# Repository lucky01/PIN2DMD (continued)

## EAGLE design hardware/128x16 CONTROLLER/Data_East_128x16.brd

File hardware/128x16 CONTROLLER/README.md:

# PIN2DMD - 128x16 DOT MATRIX CONTROLLER BOARD

This are the PCB files for the Dot Matrix Contoller Board like used in early Data East machines 
e.g Checkpoint, Hook, Star Trek and Teenage Mutant Ninja Turtles. It is needed to connect these
machines to the PIN2DMD Nucleo shield. PCB design by Rappelbox, UncleSash and Lucky1

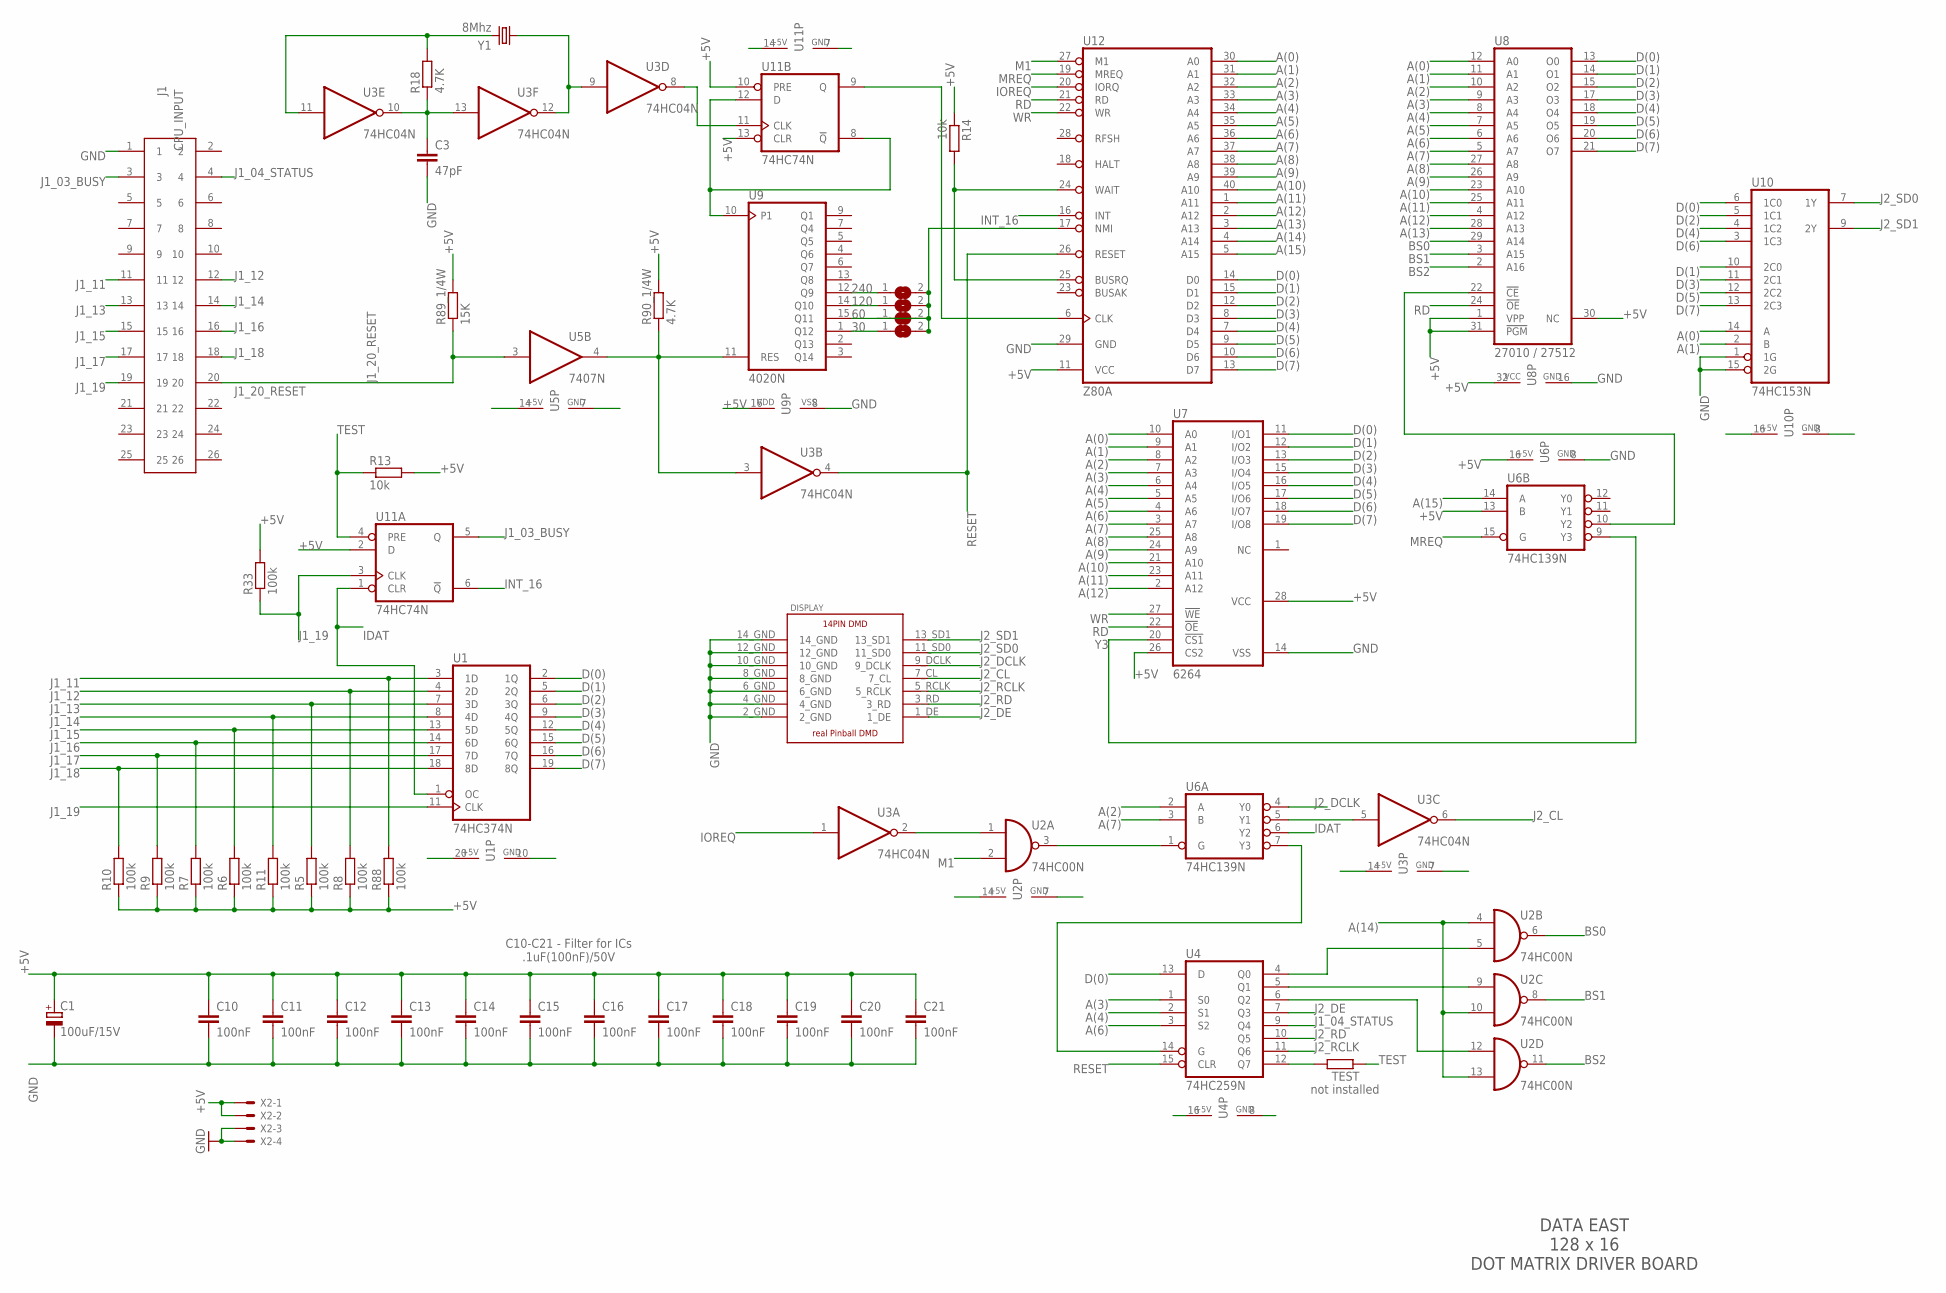
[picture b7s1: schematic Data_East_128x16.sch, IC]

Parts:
C1: 100uF/15V; E2,5-7
C3: 47pF; C050-025X075
C10, C11, C12, C13, C14, C15, C16, C17, C18, C19, C20, C21: 100nF; C050-025X075
CPU_INPUT: J1; 61202622323
DISPLAY: PINBALL_DMD_HEADER_MALE; 14_PIN_DMD_MALE
R5, R6, R7, R8, R9, R10, R11, R33, R88: 100k; 0207/7
R13, R14: 10k; 0207/7
R18, R90_1/4W: 4.7K; 0207/7
R89_1/4W: 15K; 0207/7
SJ2, SJ4, SJ5, SJ6: SJ
TEST: R-EU_0207/7; 0207/7
U1: 74HC374N; DIL20
U2: 74HC00N; DIL14
U3: 74HC04N; DIL14
U4: 74HC259N; DIL16
U5: 7407N; DIL14
U6: 74HC139N; DIL16
U7: 6264; DIL28-6
U8: 27010 / 27512; DIL32
U9: 4020N; DIL16
U10: 74HC153N; DIL16
U11: 74HC74N; DIL14
U12: Z80A; DIL40
X2: KK-156-4
Y1: 8Mhz; HC49U70

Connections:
30: SJ6.1, U9.1 (Q12)
60: SJ2.2, SJ4.2, SJ5.1, SJ5.2, SJ6.2, U9.15 (Q11), U12.17 (NMI)
120: SJ4.1, U9.14 (Q10)
240: SJ2.1, U9.12 (Q9)
+5V: C1.+, C10.1, C11.1, C12.1, C13.1, C14.1, C15.1, C16.1, C17.1, C18.1, C19.1, C20.1, C21.1, R5.1, R6.1, R7.1, R8.1, R9.1, R10.1, R11.1, R13.2, R14.1, R33.2, R88.1, R89_1/4W.2, R90_1/4W.2, U1.20 (VCC), U2.14 (VCC), U3.14 (VCC), U4.16 (VCC), U5.14 (VCC), U6.13 (B), U6.16 (VCC), U7.26 (CS2), U7.28 (VCC), U8.1 (VPP), U8.30 (NC), U8.31 (!PGM), U8.32 (VCC), U9.16 (VDD), U10.16 (VCC), U11.2 (D), U11.10 (PRE), U11.13 (CLR), U11.14 (VCC), U12.11 (VCC), X2.1, X2.2
A(0): U7.10 (A0), U8.12 (A0), U10.14 (A), U12.30 (A0)
A(1): U7.9 (A1), U8.11 (A1), U10.2 (B), U12.31 (A1)
A(2): U6.2 (A), U7.8 (A2), U8.10 (A2), U12.32 (A2)
A(3): U4.1 (S0), U7.7 (A3), U8.9 (A3), U12.33 (A3)
A(4): U4.2 (S1), U7.6 (A4), U8.8 (A4), U12.34 (A4)
A(5): U7.5 (A5), U8.7 (A5), U12.35 (A5)
A(6): U4.3 (S2), U7.4 (A6), U8.6 (A6), U12.36 (A6)
A(7): U6.3 (B), U7.3 (A7), U8.5 (A7), U12.37 (A7)
A(8): U7.25 (A8), U8.27 (A8), U12.38 (A8)
A(9): U7.24 (A9), U8.26 (A9), U12.39 (A9)
A(10): U7.21 (A10), U8.23 (A10), U12.40 (A10)
A(11): U7.23 (A11), U8.25 (A11), U12.1 (A11)
A(12): U7.2 (A12), U8.4 (A12), U12.2 (A12)
A(13): U8.28 (A13), U12.3 (A13)
A(14): U2.4 (I0), U2.10 (I1), U2.13 (I1), U12.4 (A14)
A(15): U6.14 (A), U12.5 (A15)
BS0: U2.6 (O), U8.29 (A14)
BS1: U2.8 (O), U8.3 (A15)
BS2: U2.11 (O), U8.2 (A16)
D(0): U1.2 (1Q), U4.13 (D), U7.11 (I/O1), U8.13 (O0), U10.6 (1C0), U12.14 (D0)
D(1): U1.5 (2Q), U7.12 (I/O2), U8.14 (O1), U10.10 (2C0), U12.15 (D1)
D(2): U1.6 (3Q), U7.13 (I/O3), U8.15 (O2), U10.5 (1C1), U12.12 (D2)
D(3): U1.9 (4Q), U7.15 (I/O4), U8.17 (O3), U10.11 (2C1), U12.8 (D3)
D(4): U1.12 (5Q), U7.16 (I/O5), U8.18 (O4), U10.4 (1C2), U12.7 (D4)
D(5): U1.15 (6Q), U7.17 (I/O6), U8.19 (O5), U10.12 (2C2), U12.9 (D5)
D(6): U1.16 (7Q), U7.18 (I/O7), U8.20 (O6), U10.3 (1C3), U12.10 (D6)
D(7): U1.19 (8Q), U7.19 (I/O8), U8.21 (O7), U10.13 (2C3), U12.13 (D7)
GND: C1.-, C3.2, C10.2, C11.2, C12.2, C13.2, C14.2, C15.2, C16.2, C17.2, C18.2, C19.2, C20.2, C21.2, CPU_INPUT.1, DISPLAY.2_GND, DISPLAY.4_GND, DISPLAY.6_GND, DISPLAY.8_GND, DISPLAY.10_GND, DISPLAY.12_GND, DISPLAY.14_GND, U1.10 (GND), U2.7 (GND), U3.7 (GND), U4.8 (GND), U5.7 (GND), U6.8 (GND), U7.14 (VSS), U8.16 (GND), U9.8 (VSS), U10.1 (1G), U10.8 (GND), U10.15 (2G), U11.7 (GND), U12.29 (GND), X2.3, X2.4
IDAT: U1.1 (OC), U6.6 (Y2), U11.1 (CLR)
INT_16: U11.6 (!Q), U12.16 (INT)
IOREQ: U3.1 (I), U12.20 (IORQ)
J1_03_BUSY: CPU_INPUT.3, U11.5 (Q)
J1_04_STATUS: CPU_INPUT.4, U4.9 (Q4)
J1_11: CPU_INPUT.11, R88.2, U1.3 (1D)
J1_12: CPU_INPUT.12, R8.2, U1.4 (2D)
J1_13: CPU_INPUT.13, R5.2, U1.7 (3D)
J1_14: CPU_INPUT.14, R11.2, U1.8 (4D)
J1_15: CPU_INPUT.15, R6.2, U1.13 (5D)
J1_16: CPU_INPUT.16, R7.2, U1.14 (6D)
J1_17: CPU_INPUT.17, R9.2, U1.17 (7D)
J1_18: CPU_INPUT.18, R10.2, U1.18 (8D)
J1_19: CPU_INPUT.19, R33.1, U1.11 (CLK), U11.3 (CLK)
J1_20_RESET: CPU_INPUT.20, R89_1/4W.1, U5.3 (I)
J2_CL: DISPLAY.7_CL, U3.6 (O)
J2_DCLK: DISPLAY.9_DCLK, U6.4 (Y0)
J2_DE: DISPLAY.1_DE, U4.7 (Q3)
J2_RCLK: DISPLAY.5_RCLK, U4.11 (Q6)
J2_RD: DISPLAY.3_RD, U4.10 (Q5)
J2_SD0: DISPLAY.11_SD0, U10.7 (1Y)
J2_SD1: DISPLAY.13_SD1, U10.9 (2Y)
M1: U2.2 (I1), U12.27 (M1)
MREQ: U6.15 (G), U12.19 (MREQ)
unnamed: C3.1, R18.1, U3.10 (O), U3.13 (I)
unnamed: R18.2, U3.11 (I), Y1.2
unnamed: U3.9 (I), U3.12 (O), Y1.1
unnamed: TEST.2, U4.12 (Q7)
unnamed: U3.8 (O), U11.11 (CLK)
unnamed: U9.10 (P1), U11.8 (!Q), U11.12 (D)
unnamed: R90_1/4W.1, U3.3 (I), U5.4 (O), U9.11 (RES)
unnamed: U11.9 (Q), U12.6 (CLK)
unnamed: R14.2, U12.24 (WAIT), U12.25 (BUSRQ)
unnamed: U3.5 (I), U6.5 (Y1)
unnamed: U2.5 (I1), U4.4 (Q0)
unnamed: U2.1 (I0), U3.2 (O)
unnamed: U2.3 (O), U6.1 (G)
unnamed: U2.9 (I0), U4.5 (Q1)
unnamed: U4.14 (G), U6.7 (Y3)
unnamed: U2.12 (I0), U4.6 (Q2)
unnamed: U6.10 (Y2), U8.22 (!CE)
RD: U7.22 (!OE), U8.24 (!OE), U12.21 (RD)
RESET: U3.4 (O), U4.15 (CLR), U12.26 (RESET)
TEST: R13.1, TEST.1, U11.4 (PRE)
WR: U7.27 (!WE), U12.22 (WR)
Y3: U6.9 (Y3), U7.20 (!CS1)

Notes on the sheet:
C10-C21 - Filter for ICs .1uF(100nF)/50V
DATA EAST 128 x 16 DOT MATRIX DRIVER BOARD
not installed

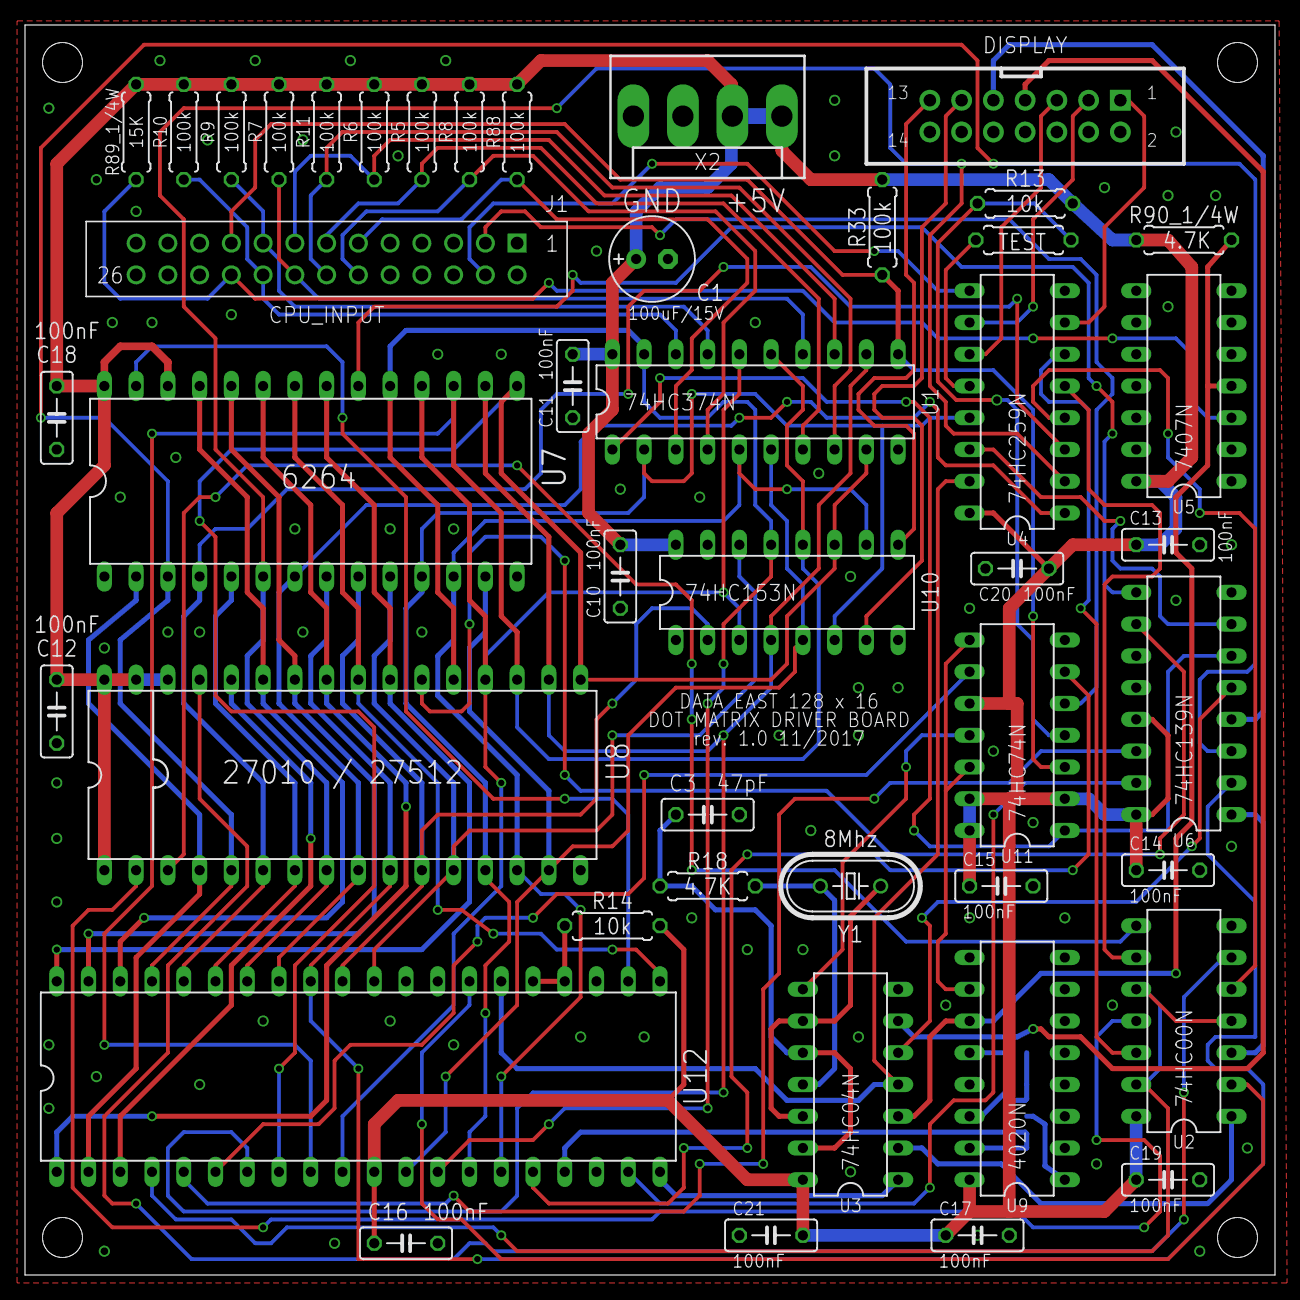
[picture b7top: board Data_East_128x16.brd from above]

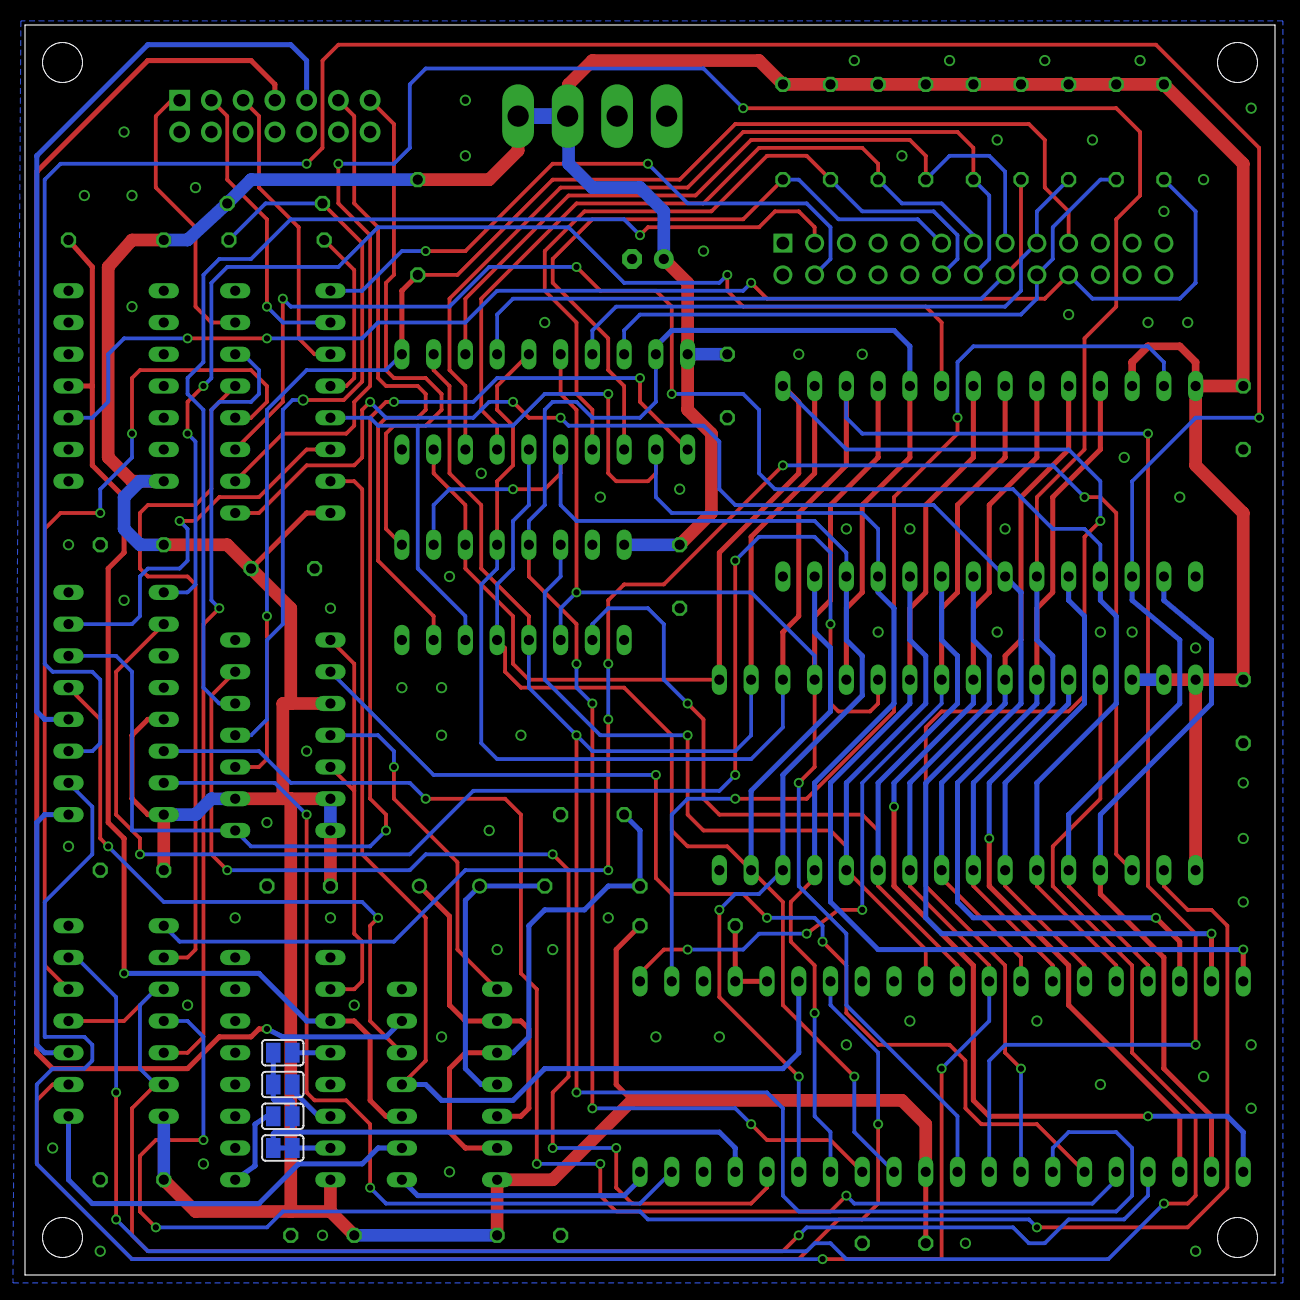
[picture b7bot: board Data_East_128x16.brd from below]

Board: 2 copper layers, 100.0 x 100.0 mm, 49 parts (4 on the bottom side), 79 nets.

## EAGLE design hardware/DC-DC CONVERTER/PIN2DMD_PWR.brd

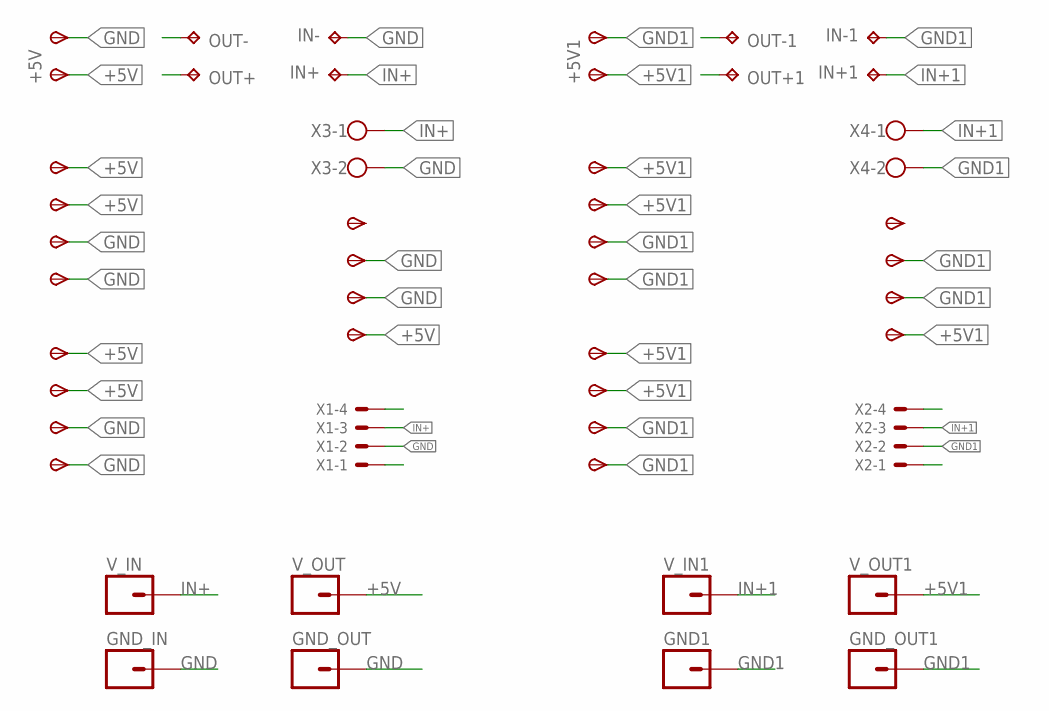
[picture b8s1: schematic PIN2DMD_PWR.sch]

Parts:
+5V, +5V1: TPSPAD1-20Y; P1-20Y
GND1: M01PTH; 1X01
GND_IN: M01PTH; 1X01
GND_OUT, GND_OUT1: M01PTH; 1X01
IN+, IN+1: TPPAD1-20; P1-20
IN-, IN-1: TPPAD1-20; P1-20
OUT+, OUT+1: TPPAD1-20; P1-20
OUT-, OUT-1: TPPAD1-20; P1-20
TP1, TP2, TP3, TP4, TP5, TP6, TP7, TP8, TP9, TP10, TP11, TP12, TP13, TP14, TP15, TP16, TP17, TP18, TP19, TP20, TP21, TP22, TP23, TP24, TP25, TP26: TPSPAD1-20Y; P1-20Y
V_IN, V_IN1: M01PTH; 1X01
V_OUT, V_OUT1: M01PTH; 1X01
X1, X2: KK-156-4
X3, X4: W237-102

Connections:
+5V: +5V.TP, OUT+.TP, TP5.TP, TP6.TP, TP7.TP, TP8.TP, TP13.TP, V_OUT.1
+5V1: +5V1.TP, OUT+1.TP, TP17.TP, TP18.TP, TP19.TP, TP20.TP, TP26.TP, V_OUT1.1
GND: GND_IN.1, GND_OUT.1, IN-.TP, OUT-.TP, TP1.TP, TP3.TP, TP4.TP, TP9.TP, TP10.TP, TP11.TP, TP12.TP, X1.2, X3.2
GND1: GND1.1, GND_OUT1.1, IN-1.TP, OUT-1.TP, TP14.TP, TP15.TP, TP16.TP, TP21.TP, TP22.TP, TP24.TP, TP25.TP, X2.2, X4.2
IN+: IN+.TP, V_IN.1, X1.3, X3.1
IN+1: IN+1.TP, V_IN1.1, X2.3, X4.1

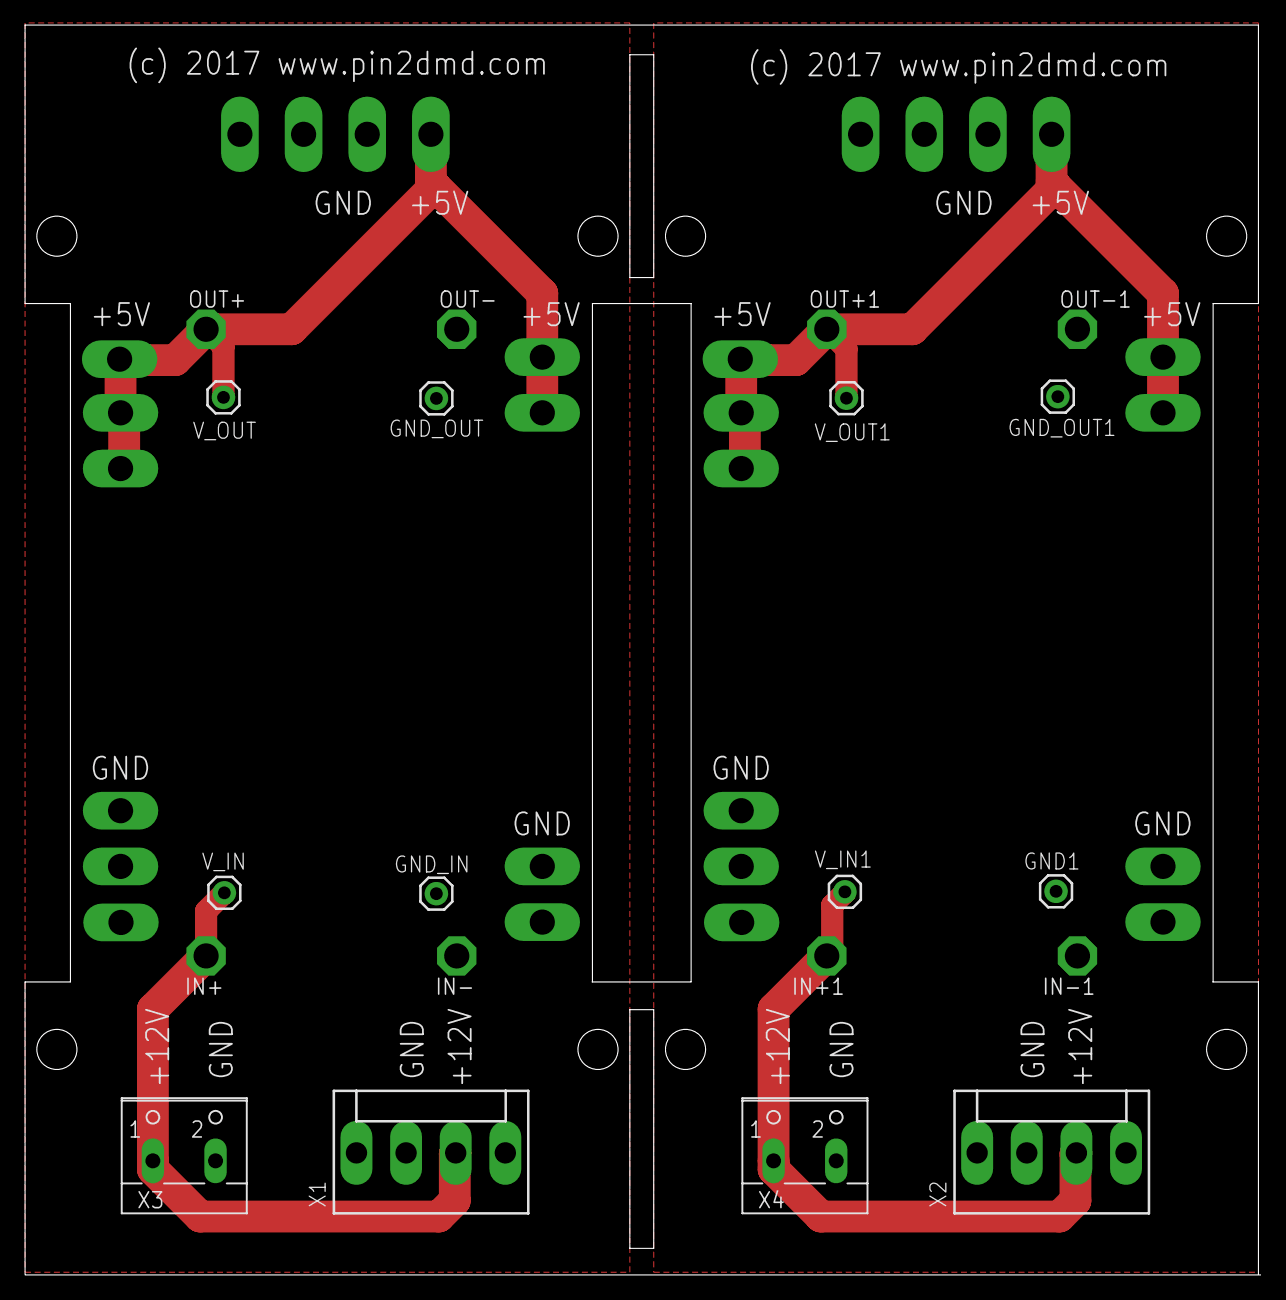
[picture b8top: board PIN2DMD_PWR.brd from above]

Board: 2 copper layers, 98.6 x 99.7 mm, 48 parts (0 on the bottom side), 6 nets.

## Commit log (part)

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2016-05-26 :space_invader: Added .gitattributes & .gitignore files
2016-05-26 update docs
2016-06-15 New version 2.21
    fix for activation key upload
2016-06-16 New version 2.22
    fix for vpin full color output
2016-06-22 New version 2.24
    fix for display errors in SAM mode
2016-06-27 New Version 2.26
    - SAM sync on OE
2016-06-29 New Version 2.28
    remove waiting for output loop
2016-07-06 updated pinout
2016-08-01 New version V2.32
    - added realpin Capcom support
    - added realpin Gottlieb mode for early machines (1992)
    - adjusted Gottlieb modes to latest vpinmame
    - added onscreen menu (hold config/blue button during boot) for basic
    config
    - first release with wifi html interface (see flash.md)
2016-09-08 updated wifi upgrade procedure
2016-09-13 new go-dmd compatible hardware layout
2016-12-24 new pin2dmd tool release 2.36
    - added advanced palette editing
    - added upload button to frontend
    - support for signal enhancer
2016-12-24 new dmddevice.dll driver for VPinMame 2.8 integration
2016-12-24 tool release 2.36
2016-12-24 new version 2.36 with license fix
2017-01-06 added XDMD dlls with dmddevice support for PinballX and UltraDMD
2017-02-22 minor fix in layout
2017-02-22 updated dmddevice.dll
2017-03-24 New Version 2.38
    - fix bitorder for DataEast and Whitestar machines
    - improved processing of fsq playback for Frame replacement and
    ColorMask
2017-04-05 added schematics as pdf
2017-04-07 new dmddevice version with patched libusb
    searches for libusbk in the same directory dmddevice.dll is located in.
    That problem is also adressed by this microsoft patch
    https://www.microsoft.com/de-de/download/details.aspx?id=26767
2017-05-16 fix crash in dmddevice.dll
2017-05-25 Changed error message handling
    Display "pin2dmd not found" message only when no device attached. Skip
    message when device not accessible.
2017-06-21 New Version 2.40
    - fix bug in palette switching
    - improve dump routine on slow USB connection
2017-09-08 move V3 shield schematics and layout into subfolder
2017-09-08 schematics and layout of DC-DC converter breakout board
2017-09-08 firmware for Nucleo-144 STM32F429ZI board
2017-10-04 updated layout of Nucleo shield
    - fix missing connection from pinball input P3 to RN2
    - cosmetics in the schematics by UncleSash
2017-10-10 optimized PCB layout by UncleSash
2017-10-10 New version 2.03 of XL firmware
    - automatically reset config if no valid values are found
2017-10-10 updated Nucleo shield 4.02
    updated labels in schematic
    optimized layout (by UncleSash)
2017-10-13 updated dmddevice.dll
    new compiler settings
2017-10-27 new firmware 2.45
    - fix bug with SD card reader
    - fix reset crash in pin2dmd.exe tool
    - updated dmddevice.dll with features from latest editor version
2017-11-01 new version 2.46
    fix vpin crash after severeal starts
2017-11-03 new version 2.47
    - fix load of initiall palette from SD
2017-11-08 new version 2.49
    fix output crash
2017-11-18 new version 2.08
    Added support for upgrade from SD card. Simply copy pin2dmd_xl.upd file
    to SD card and reset.
2017-11-23 new version 2.50
    fixed frame not displayed when using ColMask with machine types not
    supporting ColMask (early Gottlieb)
2017-12-15 new version 2.52
    fix usb close bug causing crash when diconnecting usb
2017-12-28 updated ReadMe for 128x16 controller board
2018-01-12 add acryl frame design
2018-01-13 XL firmware version 2.09 for custom board
2018-01-13 added README for custom boards
2018-01-14 new firmware version 2.10 for XL
2018-02-06 new version 2.12 for XL
    - improved editor live preview support
    - change handling of single colmask triggers
    - fix upload to SD from USB
2018-03-01 new version 2.55
    - implemented handling for follow hash
    - minor fixes
2018-04-08 new version 2.12 for XL
    added dfu file
2018-06-29 updated x64 versions
2018-07-17 updated dmddevice.dll
    fix bug when loading small palette files
2018-08-08 new version V2.57
    - fix memory problem with large projects
2018-08-30 layout for EVO128x32 pcb
2018-11-26 new version 2.60
    - unified codebase and version number for 192x64 and 128x32
    - reworked output code to improve speed and save memory (50%)
    - increased color depth for 192x64
    - fixed colorization and init code for Capcom
    - improved speed and fixes for DataEast 128x16 code
    - fixed minor bugs in bootloader (update through USB to update bootloader code)
2019-01-10 new version v2.61
    - fix display problems with some panels
2019-02-21 new version v2.63
    - fix some problems in pinmame mode
2019-02-23 new version v2.64 add dfu files
2019-03-08 new version v3.00 - based on STM32 HAL core library - added new colorization modes (colmask layered, replace follow, replace masked)
2019-05-09 add frames for 192x16 P2 and P2.5 dotpitch panels
2019-07-09 new version v2.67 - fix rare sync problem with some WPC DMD Controllers
2019-07-31 added component list to 128x16 controller psb
2019-07-31 rename CUSTOM firmware folder to CUSTOM_XL
2019-07-31 add partlist for 128x16 controller board
2019-08-01 EVO128x16 pcb layout
2019-08-01 new version v3.00 - based on hardware abstraction layer library for better portability to different hardware - added autodetection for real pinball machines when in vpin mode (default) - added displa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
2019-08-01 optimize EVO128x32 pcb layout
2019-08-01 add pcb layout and ordering information for EVO128x16 and EVO192x64
2019-08-08 new version v3.02 - make old palette switch method in freezy DLL work
2019-08-12 new version v3.03 - improve 128x16 sync
2019-09-01 minor layout change
2019-09-25 new version v3.05 - add usb raw transfer directly into displaybuffer - show activation status in onscreen menu (UID)
2019-10-10 add PoC version of MK66 firmware
2019-12-15 add Win64 and MacOSX version
2019-12-30 added P-ROC integration example
2020-01-08 fix silkscreen
2020-01-16 - add Sleic and Inder to tool - fix bug in dump routine for certain machine types
2020-01-21 new version v3.07 - fix onscreen menu buttons for Nucleo
2020-01-24 new version v3.08 - add support for HomePin
2020-02-07 new version v3.09 - fix config save function with old tool
2020-03-24 new version v3.11 - fix first frame for ColorMask layered mode - fix detection of unmasked frames in ColorMask layered mode - allow Event with same hash as colorizations - fix bug in event handling
2020-05-04 new version v3.12 - change behaviour of "Replace Masked" mode like suggested by DJRobX - don´t retrigger ColorMask layered scene if scene is already loaded - create dummy file with serial on SD if no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
2020-06-21 new version v3.13 - add optimized routine for 128x32 display on XL displays (VPIN) - fix colorization on XL displays in dmddevice.dll - use faster RGB24 routine in dmddevice.dll
2020-07-13 new version v3.15 - fix tests in onscreen menu
2020-07-19 update EVO192x64 pcb
2020-10-04 new version v3.16 - fix event keyframe only sent once - suppress subsequent events with the same ID
2020-10-20 new version v3.17 - enable to take a frame within a lcm scene as trigger to start the lcm scene.
2020-10-25 DE - SEGA - STERN power adapter pcb Designed by Rene Venema
2020-11-30 update EVO128x32 to V1.4 - add TTL level UART TX - connect 5V pinheader to DC-DC converter input
2021-01-07 new version v3.20 - migration release to version 4.x - fix masked replace mode for some devicemodes - refresh flash pal storage on firmware update
2021-01-07 new version v4.00 - implement 64color for all devicemodes - optimize/speedup create framebuffer routines for all coloring modes
2021-01-13 fix communication with latest pinmame version
2021-01-18 new version v4.02 - better timing accuracy in real pin dump
2021-01-22 new version V4.03 - fix 64 color version of Capcom
2021-01-29 fix lcm mode for 64 colors
2021-02-02 new version v4.05 - fix WPC 64color colormask mode
2021-02-03 fix broken eagle files
2021-02-09 fix 64color lcm in dmddevice.dll
2021-02-17 new version v4.07 - optimized input routine for DE128x16
2021-02-17 fix binary files
2021-03-05 new version v4.08 - improve load speed of LCM scenes for real pinball machines
2021-03-29 fix problem with Layered Replace Mask
2021-04-12 refresh gerber files
2021-06-18 new version v4.11 - add support for EVO HD 256x64 - add support for DotMation on XL 192x64
2021-06-18 add EVO256x64 pcb layout
2021-06-30 new version v4.12 - improve compatibility to old freezy.dll - set PAL STORAGE to RAM to make colorization work with old freezy versions
2021-07-08 fix crash on sequence scenes
2021-07-12 new version V4.14 - fix sequence sync broken in V4.13
2021-07-14 new version v4.15 - fix first frame no displayed in sequence modes
2021-07-23 fix BOM of 192x64
2021-08-05 new version v4.18 - fix boot for STM32F407 on EVO board
2021-09-02 new version v4.20 - fix colormask timer issue
2021-09-10 new version v4.22 - fix more SD card issues on EVO HD
2021-09-16 new version v4.24 - fix events with palstorage set to flash
2021-10-29 new version V4.26 - improve keyframe handling
2021-11-28 new version V4.28 - add support for alternative row signaling on HD
2021-12-07 new version V4.29 - add some nullpointer checks
2022-01-26 add RGB24 routines for HD
2022-02-07 new version V4.31 - scale down HD projects on 128x32
2022-02-25 new version V4.33 - fix issue with single real pin export and 64 color palettes - add 2bit 128x32 on XL mode
2022-03-18 new version V4.35 - allow more than 256 palettes - fix lcm issue in dmddevice.dll
2022-03-24 fix colorization of 16shade source on HD
2022-04-23 new version V4.37 - fix issue with DE128x16 - fix init of new chipset panels on MK66
    changes to mddevice.dll
    - use dmdext.ini instead of dmddevice.ini to allow second display with dmdscreen.dll driver and own dmddevice.ini settings.
    Makes Gottlieb Strikes'n Spares work with latest vpinmame.dll
2022-05-09 update dmddevice.dll and remove dmdExt.dll from zip archive
2022-05-17 new version V4.38 - fix RS232 TX on HD
2022-06-19 update dmddevice.dll - use dmddevice.ini instead of dmdext.ini - forward device specific calls to dmdext
2022-07-15 new version V4.40 - add support for Capcom 256x64 on Pin2DMD HD update dmddevice.dll
2022-08-01 update dmddevice.dll / pin2color.dll - add colorization support for alphanumeric tables - add dump function for alphanumeric frames to alphadump folder
2022-08-16 update dmddevice.dll / pin2color.dll - fix smb3 colorization
2022-08-31 new version V4.41 - fix update on non EVO HD pcbs - increase cpu clock startup timeout
2022-09-17 - add DFU function to 64bit tool
2022-10-21 new version V4.42
    - add support for version check to colorizations for better compatibility
    - display rgb sequence as text in onscreen menu
2022-10-25 new version V4.43
2022-11-20 update pin2color to latest
2022-12-29 new version V4.45 - add support for new coloring mode ColorMask Loop - fix colorization issue on XL boards - fix colorization issue on MK66 boards
2022-12-29 update dmddevice.dll add support for latest coloring modes "Replace no retrigger" and "ColorMask Loop"
2022-12-30 new version V4.46 -fix nullpointer exception
2023-01-21 new version V4.48 - final fix of rare issue with EVO boards needing reset to start after poweron. Full install of firmware needed with DFU or BIN file. - fix REPLACE_NO_RETRIGGER coloring mode replay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
2023-02-28 new version V4.50 - add support for DevEBox PIN2DMD HD Shield
2023-05-10 new version V4.51 - don´t retrigger ColMaskLoop and Replace_No_Retrigger mode even if different start keyframes are used.
2023-09-11 update tool and drivers
2024-03-04 add sysXdmd binary
2024-06-27 update sysXdmd to v1.01 - fix display issue
2024-09-25 new version v2.54 for PIN2DMD HD - add experimental support for SM16380SH chipset (close J2 and J3) - fix brightness routine for SM16380SC and ICND2153
2024-10-14 new version v4.55 for pin2dmd HD - fix display issue for SM16380SH chipset on some brightness levels - improve brightness range for SM16380SH PWM chipset
2025-01-31 - added config files for DMDMK66 - added pin2color plugin for release version v2.3 of dmdext
2025-06-04 - update pin2color plugin for dmdext version 2.3.1 - update dmddevice.dll
2025-10-08 new version v4.56 - add support for Sleic IO Moon
2025-12-14 updated pcb layout for EVO128x32 and EVO256x64
2026-01-15 new version v5.00 - fix Sleic Bike Race sync - version bump
2026-03-18 new version v5.01 - improve MMI handshake
2026-03-28 -add MMI interface to EVO192x64 pcb
2026-03-30 add pcb layout for SysXDMD and Nucleo MMI adapter
2026-04-10 new version V5.04 - add support for PIN2DMD MMI on DevEBox platform - add MMI interface to DevEBox
